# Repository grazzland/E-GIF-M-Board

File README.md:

# E-GIF-M-Board
Extendable Gateway and Industrial Firewall-ModBus

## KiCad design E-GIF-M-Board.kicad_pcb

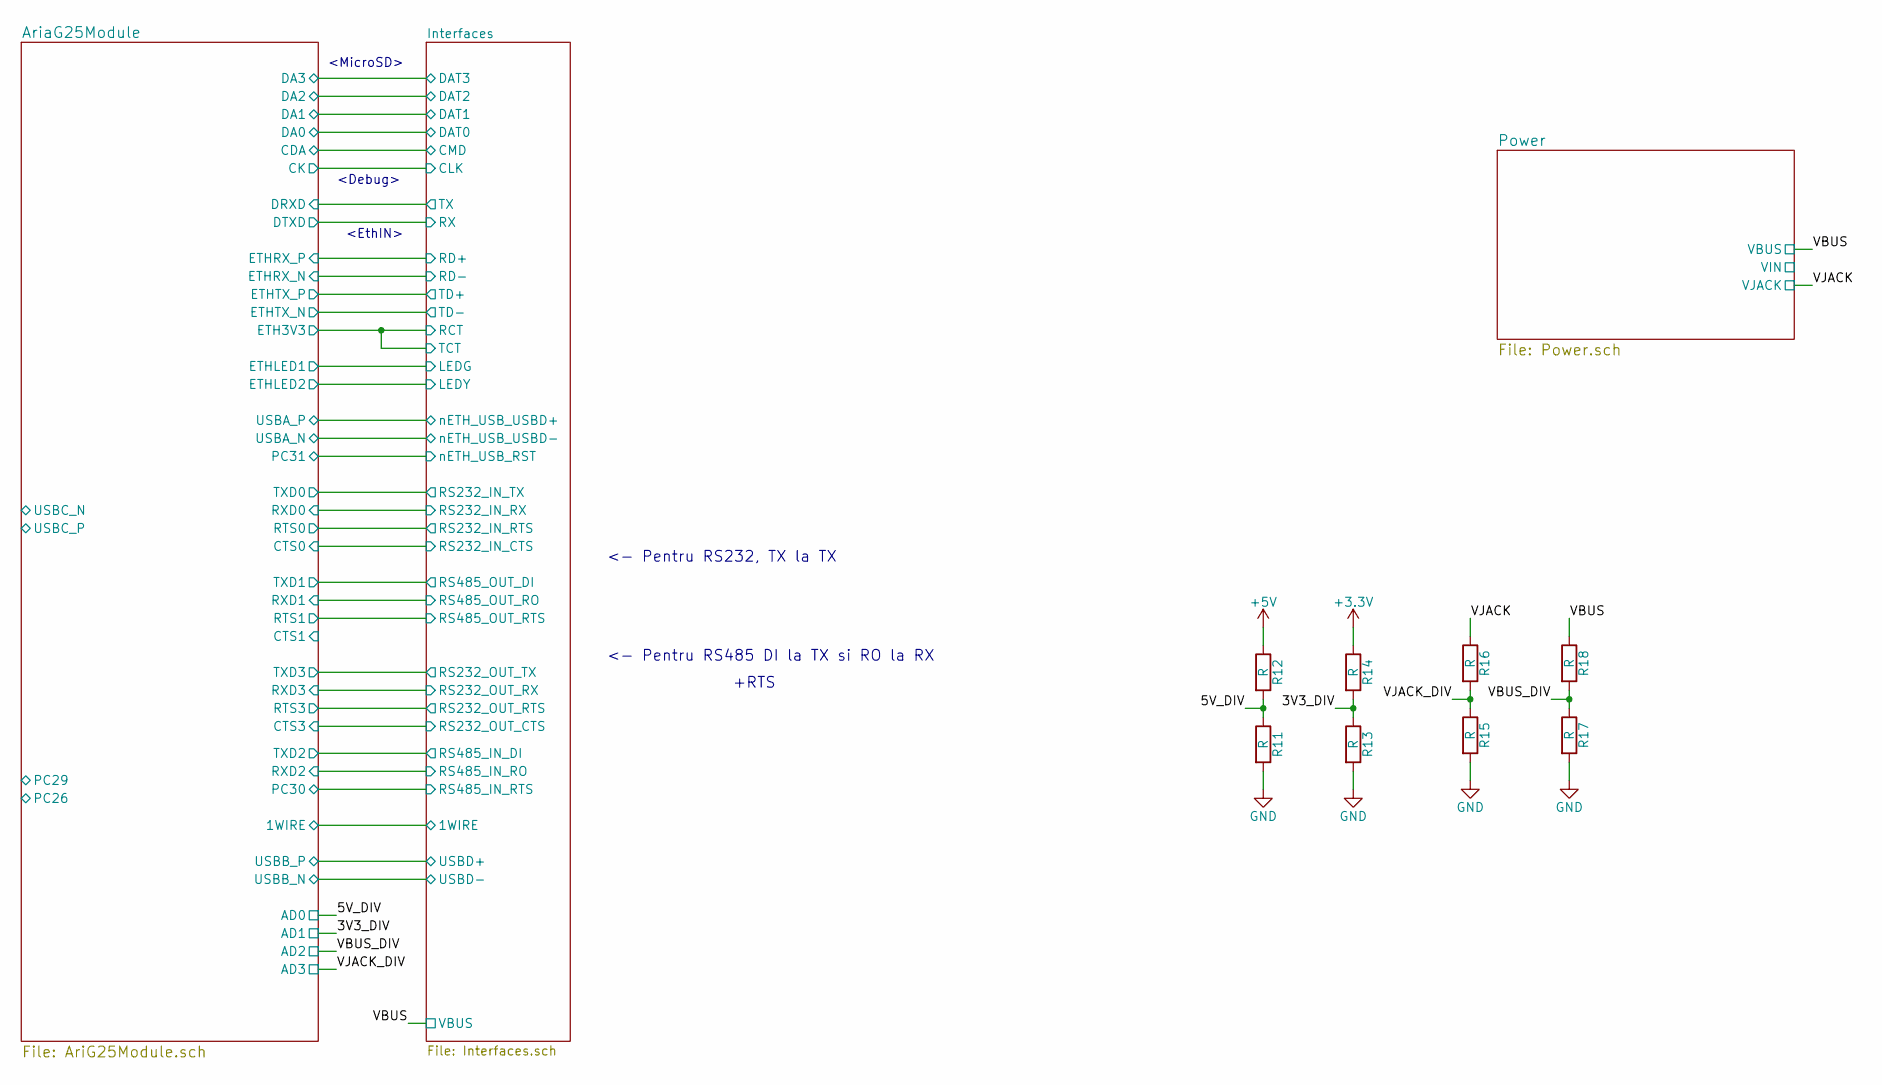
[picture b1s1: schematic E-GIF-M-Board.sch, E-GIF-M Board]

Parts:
R11, R12, R13, R14, R15, R16, R17, R18: R

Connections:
+3V3: R14.1; also elsewhere on the board
+5V: R12.1; also elsewhere on the board
/3V3_DIV: R13.1, R14.2; also elsewhere on the board
/5V_DIV: R11.1, R12.2; also elsewhere on the board
/VBUS: R18.1; also elsewhere on the board
/VBUS_DIV: R17.1, R18.2; also elsewhere on the board
/VJACK: R16.1; also elsewhere on the board
/VJACK_DIV: R15.1, R16.2; also elsewhere on the board
GND: R11.2, R13.2, R15.2, R17.2; also elsewhere on the board

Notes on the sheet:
<MicroSD>
<Debug>
<EthIN>
<- Pentru RS232, TX la TX
<- Pentru RS485 DI la TX si RO la RX
+RTS

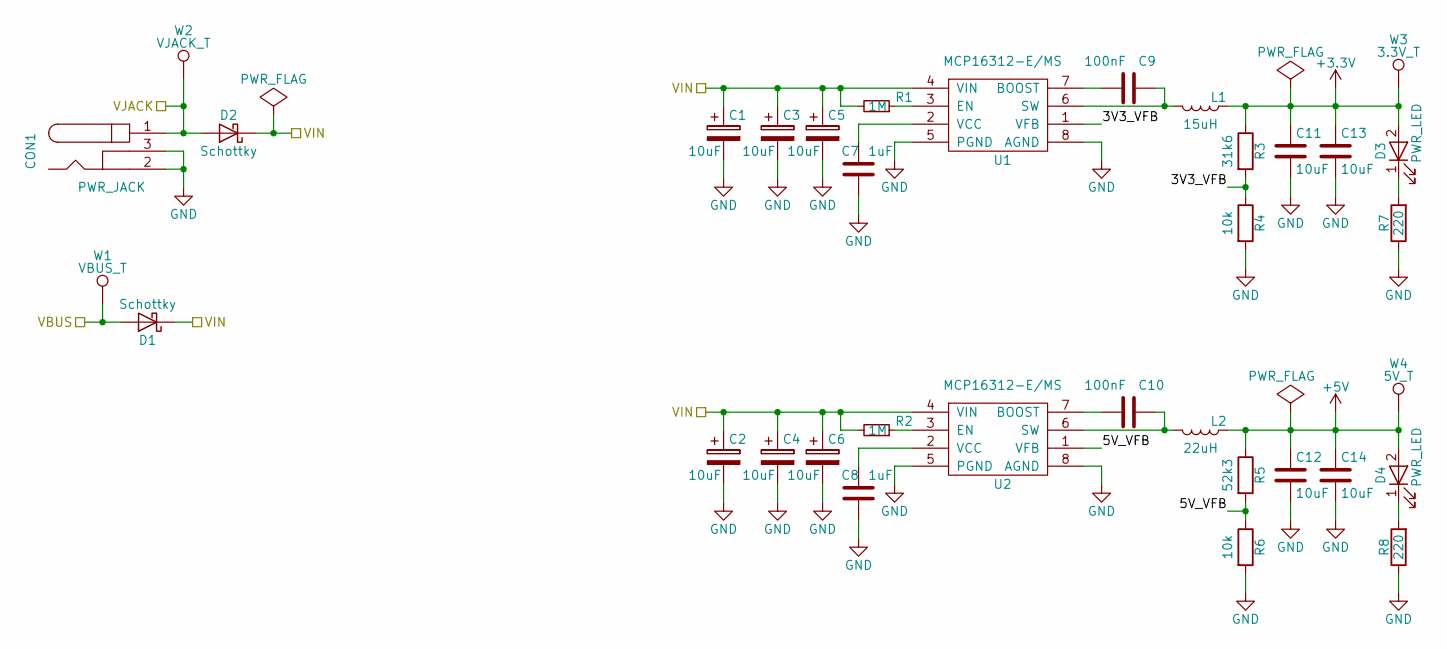
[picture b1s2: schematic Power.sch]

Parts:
C1, C2, C3, C4, C5, C6: 10uF; CP_Tantalum_Case-B_EIA-3528-21_Hand
C7, C8: 1uF; C_0603_HandSoldering
C9, C10: 100nF; C_0603_HandSoldering
C11, C12, C13, C14: 10uF; C_0603_HandSoldering
CON1: PWR_JACK; BARREL_JACK
D1, D2: Schottky; D_SMA-SMB_Universal_Handsoldering
D3, D4: PWR_LED; LED_0603
L1: 15uH; Inductor_Taiyo-Yuden_MD-5050
L2: 22uH; Inductor_Taiyo-Yuden_MD-5050
R1, R2: 1M; R_0603_HandSoldering
R3: 31k6; R_0603_HandSoldering
R4, R6: 10k; R_0603_HandSoldering
R5: 52k3; R_0603_HandSoldering
R7, R8: 220; R_0603_HandSoldering
U1, U2: MCP16312-E/MS; MSOP-8_3x3mm_Pitch0.65mm
W1: VBUS_T; Measurement_Point_Round-SMD-Pad_Small
W2: VJACK_T; Measurement_Point_Round-SMD-Pad_Small
W3: 3.3V_T; Measurement_Point_Round-SMD-Pad_Small
W4: 5V_T; Measurement_Point_Round-SMD-Pad_Small

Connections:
+3V3: C11.1, C13.1, D3.2 (A), L1.1, R3.1, W3.1; also elsewhere on the board
+5V: C12.1, C14.1, D4.2 (A), L2.1, R5.1, W4.1; also elsewhere on the board
/Power/3V3_VFB: R3.2, R4.1, U1.1 (VFB)
/Power/5V_VFB: R5.2, R6.1, U2.1 (VFB)
/Power/VIN: C1.1, C2.1, C3.1, C4.1, C5.1, C6.1, D1.1 (K), D2.1 (K), R1.2, R2.2, U1.4 (VIN), U2.4 (VIN)
/VBUS: D1.2 (A), W1.1; also elsewhere on the board
/VJACK: CON1.1, D2.2 (A), W2.1; also elsewhere on the board
GND: C1.2, C2.2, C3.2, C4.2, C5.2, C6.2, C7.2, C8.2, C11.2, C12.2, C13.2, C14.2, CON1.2, CON1.3, R4.2, R6.2, R7.1, R8.1, U1.5 (PGND), U1.8 (AGND), U2.5 (PGND), U2.8 (AGND); also elsewhere on the board
unnamed: C7.1, U1.2 (VCC)
unnamed: C8.1, U2.2 (VCC)
unnamed: C9.1, L1.2, U1.6 (SW)
unnamed: C9.2, U1.7 (BOOST)
unnamed: C10.1, L2.2, U2.6 (SW)
unnamed: C10.2, U2.7 (BOOST)
unnamed: D3.1 (K), R7.2
unnamed: D4.1 (K), R8.2
unnamed: R1.1, U1.3 (EN)
unnamed: R2.1, U2.3 (EN)

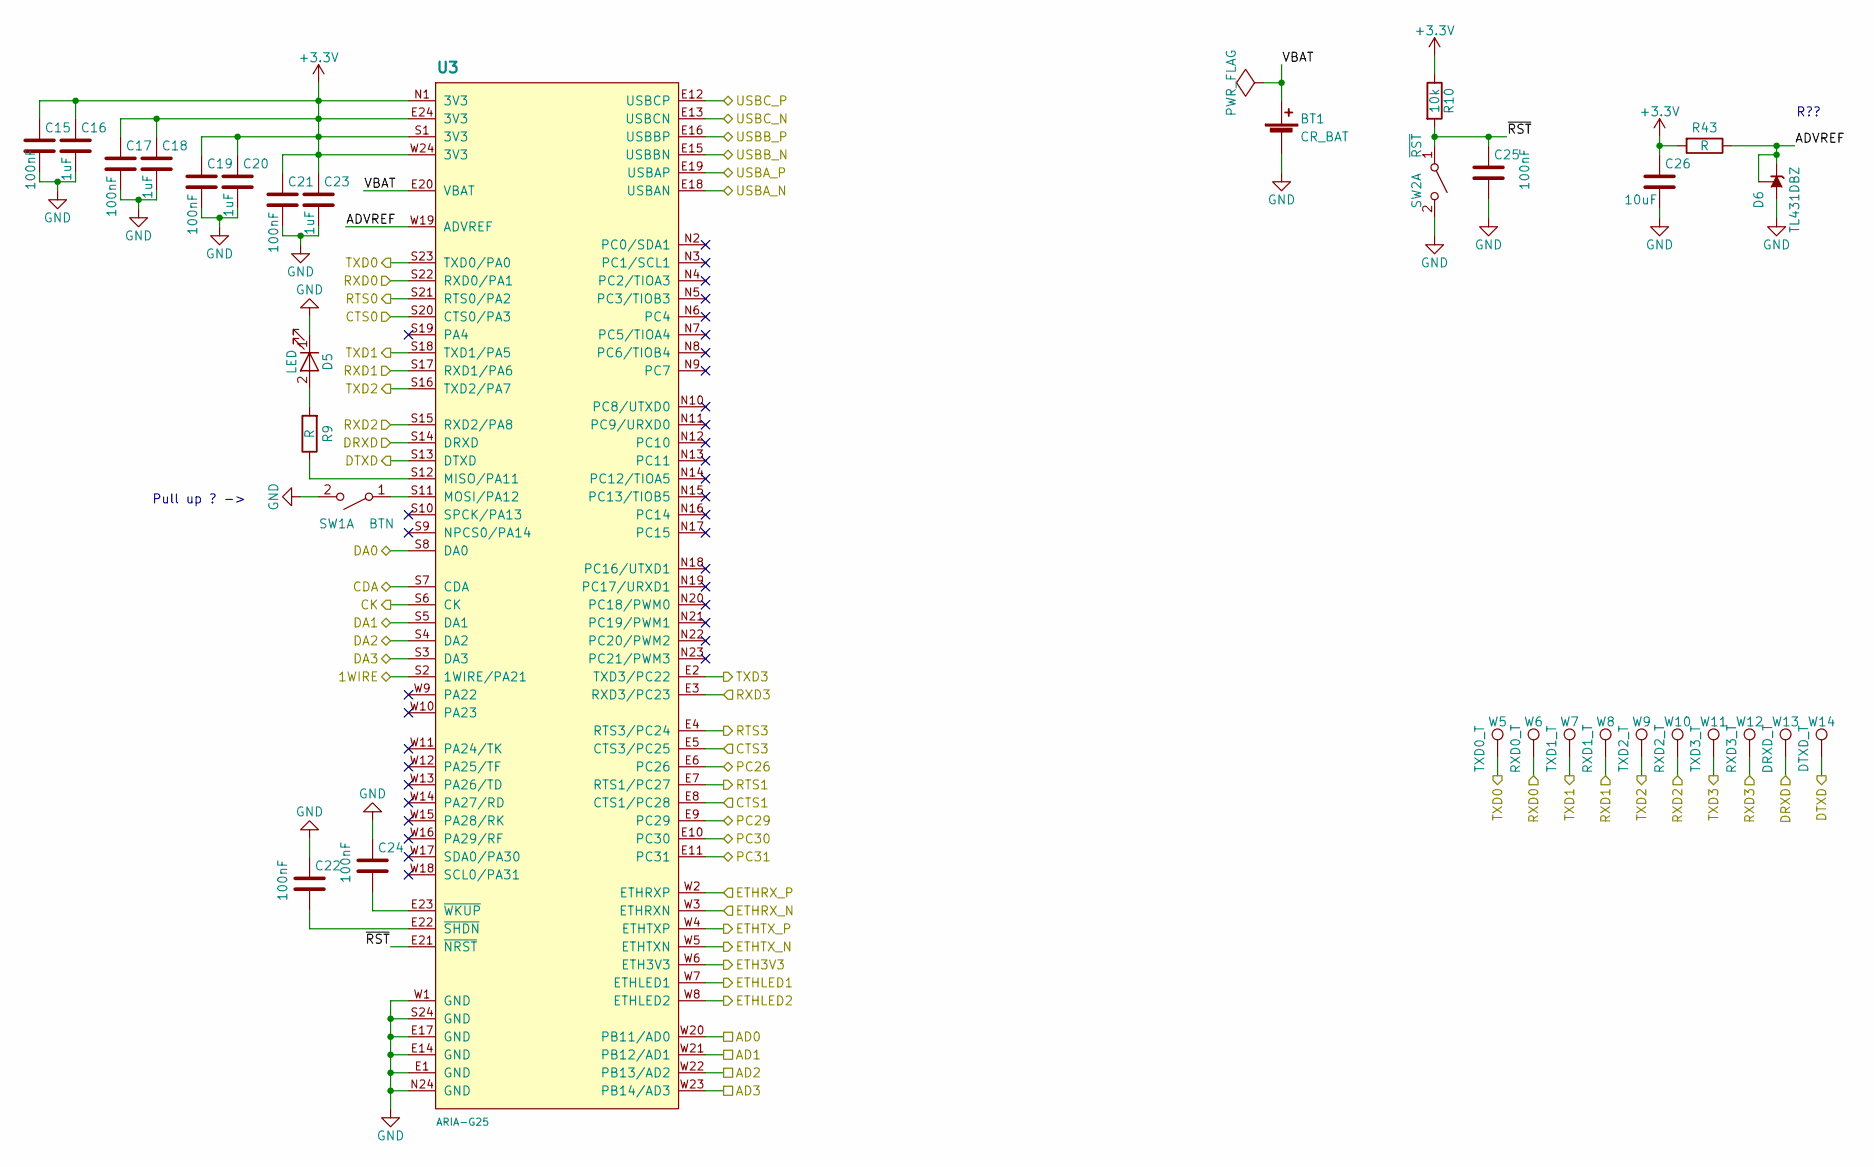
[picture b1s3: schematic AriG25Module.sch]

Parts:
BT1: CR_BAT; BatteryHolder_CoinCell_Keystone_3001
C15, C17, C19, C21, C22, C24, C25: 100nF; C_0603_HandSoldering
C16, C18, C20, C23: 1uF; C_0603_HandSoldering
C26: 10uF; C_0603_HandSoldering
D5: LED; LED_0603
D6: TL431DBZ; SOT-23
R9, R43: R; R_0603_HandSoldering
R10: 10k; R_0603_HandSoldering
SW1: BTN; SW_SPST_EVQPE1
SW2: ~RST; SW_SPST_EVQPE1
U3: ARIA-G25
W5: TXD0_T; Measurement_Point_Round-SMD-Pad_Small
W6: RXD0_T; Measurement_Point_Round-SMD-Pad_Small
W7: TXD1_T; Measurement_Point_Round-SMD-Pad_Small
W8: RXD1_T; Measurement_Point_Round-SMD-Pad_Small
W9: TXD2_T; Measurement_Point_Round-SMD-Pad_Small
W10: RXD2_T; Measurement_Point_Round-SMD-Pad_Small
W11: TXD3_T; Measurement_Point_Round-SMD-Pad_Small
W12: RXD3_T; Measurement_Point_Round-SMD-Pad_Small
W13: DRXD_T; Measurement_Point_Round-SMD-Pad_Small
W14: DTXD_T; Measurement_Point_Round-SMD-Pad_Small

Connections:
+3V3: C15.1, C16.1, C17.1, C18.1, C19.1, C20.1, C21.1, C23.1, C26.1, R10.1, R43.2, U3.E24 (3V3), U3.N1 (3V3), U3.S1 (3V3), U3.W24 (3V3); also elsewhere on the board
/3V3_DIV: U3.W21 (PB12/AD1); also elsewhere on the board
/5V_DIV: U3.W20 (PB11/AD0); also elsewhere on the board
/AriaG25Module/1WIRE: U3.S2 (1WIRE/PA21); also elsewhere on the board
/AriaG25Module/ADVREF: D6.1 (K), D6.2 (REF), R43.1, U3.W19 (ADVREF)
/AriaG25Module/CDA: U3.S7 (CDA); also elsewhere on the board
/AriaG25Module/CK: U3.S6 (CK); also elsewhere on the board
/AriaG25Module/CTS0: U3.S20 (CTS0/PA3); also elsewhere on the board
/AriaG25Module/CTS1: U3.E8 (CTS1/PC28)
/AriaG25Module/CTS3: U3.E5 (CTS3/PC25); also elsewhere on the board
/AriaG25Module/DA0: U3.S8 (DA0); also elsewhere on the board
/AriaG25Module/DA1: U3.S5 (DA1); also elsewhere on the board
/AriaG25Module/DA2: U3.S4 (DA2); also elsewhere on the board
/AriaG25Module/DA3: U3.S3 (DA3); also elsewhere on the board
/AriaG25Module/DRXD: U3.S14 (DRXD), W13.1; also elsewhere on the board
/AriaG25Module/DTXD: U3.S13 (DTXD), W14.1; also elsewhere on the board
/AriaG25Module/ETH3V3: U3.W6 (ETH3V3); also elsewhere on the board
/AriaG25Module/ETHLED1: U3.W7 (ETHLED1); also elsewhere on the board
/AriaG25Module/ETHLED2: U3.W8 (ETHLED2); also elsewhere on the board
/AriaG25Module/ETHRX_N: U3.W3 (ETHRXN); also elsewhere on the board
/AriaG25Module/ETHRX_P: U3.W2 (ETHRXP); also elsewhere on the board
/AriaG25Module/ETHTX_N: U3.W5 (ETHTXN); also elsewhere on the board
/AriaG25Module/ETHTX_P: U3.W4 (ETHTXP); also elsewhere on the board
/AriaG25Module/PC26: U3.E6 (PC26)
/AriaG25Module/PC29: U3.E9 (PC29)
/AriaG25Module/PC30: U3.E10 (PC30); also elsewhere on the board
/AriaG25Module/PC31: U3.E11 (PC31); also elsewhere on the board
/AriaG25Module/USBA_N: U3.E18 (USBAN); also elsewhere on the board
/AriaG25Module/USBA_P: U3.E19 (USBAP); also elsewhere on the board
/AriaG25Module/USBB_N: U3.E15 (USBBN); also elsewhere on the board
/AriaG25Module/USBB_P: U3.E16 (USBBP); also elsewhere on the board
/AriaG25Module/USBC_N: U3.E13 (USBCN)
/AriaG25Module/USBC_P: U3.E12 (USBCP)
/AriaG25Module/VBAT: BT1.1 (+), U3.E20 (VBAT)
/AriaG25Module/~RST: C25.1, R10.2, SW2.1 (A), U3.E21 (~NRST)
/Interfaces/RS232_IN_RTS: U3.S21 (RTS0/PA2); also elsewhere on the board
/Interfaces/RS232_IN_RX: U3.S22 (RXD0/PA1), W6.1; also elsewhere on the board
/Interfaces/RS232_IN_TX: U3.S23 (TXD0/PA0), W5.1; also elsewhere on the board
/Interfaces/RS232_OUT_RTS: U3.E4 (RTS3/PC24); also elsewhere on the board
/Interfaces/RS232_OUT_RX: U3.E3 (RXD3/PC23), W12.1; also elsewhere on the board
/Interfaces/RS232_OUT_TX: U3.E2 (TXD3/PC22), W11.1; also elsewhere on the board
/Interfaces/RS485_IN_DI: U3.S16 (TXD2/PA7), W9.1; also elsewhere on the board
/Interfaces/RS485_IN_RO: U3.S15 (RXD2/PA8), W10.1; also elsewhere on the board
/Interfaces/RS485_OUT_DI: U3.S18 (TXD1/PA5), W7.1; also elsewhere on the board
/Interfaces/RS485_OUT_RO: U3.S17 (RXD1/PA6), W8.1; also elsewhere on the board
/Interfaces/RS485_OUT_RTS: U3.E7 (RTS1/PC27); also elsewhere on the board
/VBUS_DIV: U3.W22 (PB13/AD2); also elsewhere on the board
/VJACK_DIV: U3.W23 (PB14/AD3); also elsewhere on the board
GND: BT1.2 (-), C15.2, C16.2, C17.2, C18.2, C19.2, C20.2, C21.2, C22.1, C23.2, C24.1, C25.2, C26.2, D5.1 (K), D6.3 (A), SW1.2 (B), SW2.2 (B), U3.E1 (GND), U3.E14 (GND), U3.E17 (GND), U3.GND, U3.N24 (GND), U3.S24 (GND), U3.W1 (GND); also elsewhere on the board
unnamed: C22.2, U3.E22 (~SHDN)
unnamed: C24.2, U3.E23 (~WKUP)
unnamed: D5.2 (A), R9.2
unnamed: R9.1, U3.S12 (MISO/PA11)
unnamed: SW1.1 (A), U3.S11 (MOSI/PA12)

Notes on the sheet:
R??
Pull up ? ->

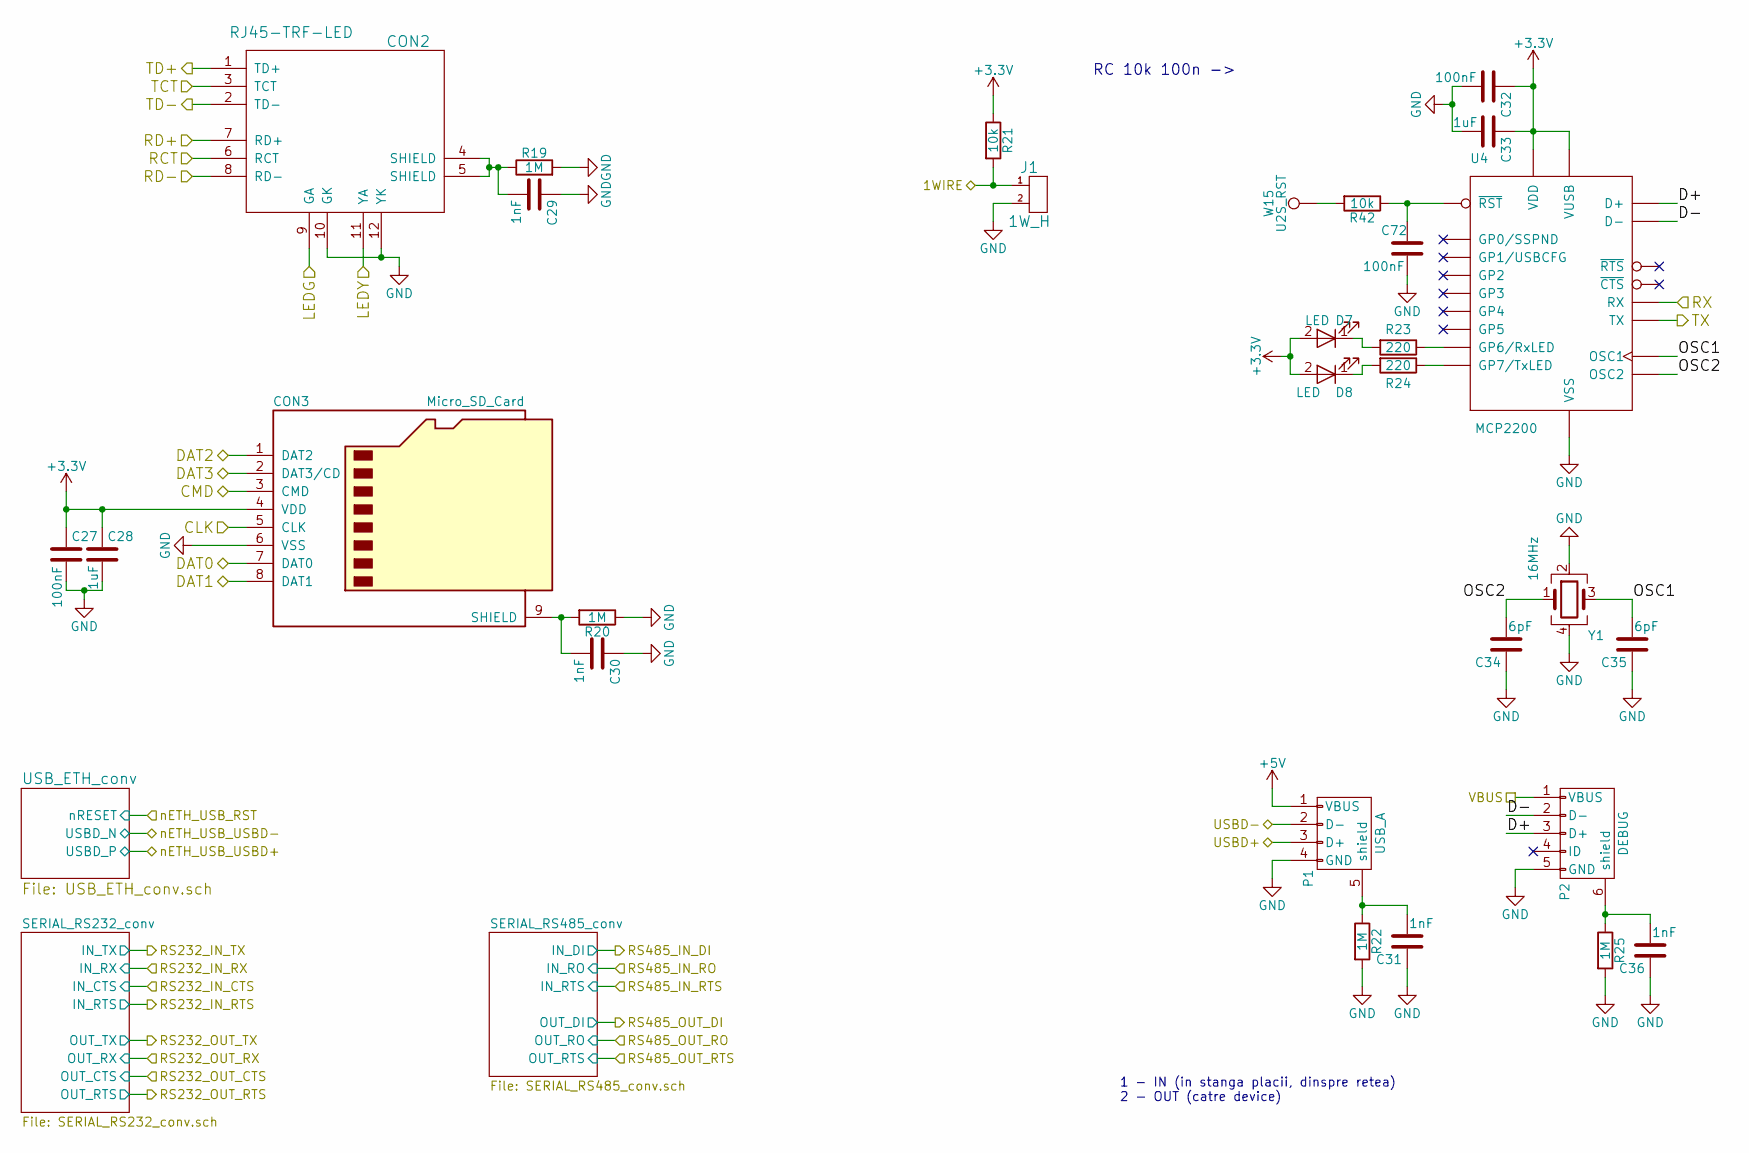
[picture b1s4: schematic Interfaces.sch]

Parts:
C27, C32, C72: 100nF; C_0603_HandSoldering
C28, C33: 1uF; C_0603_HandSoldering
C29, C30, C31, C36: 1nF; C_0603_HandSoldering
C34, C35: 6pF; C_0603_HandSoldering
CON2: RJ45-TRF-LED; RJ45_TRANSFO
CON3: Micro_SD_Card; MicroSDSocket
D7, D8: LED; LED_0603
J1: 1W_H; Pin_Header_Straight_1x02_Pitch1.27mm
P1: USB_A
P2: DEBUG; MicroUSB-B
R19, R20, R22, R25: 1M; R_0603_HandSoldering
R21, R42: 10k; R_0603_HandSoldering
R23, R24: 220; R_0603_HandSoldering
U4: MCP2200; SSOP-20_4.4x6.5mm_Pitch0.65mm
W15: U2S_RST; Measurement_Point_Round-SMD-Pad_Small
Y1: 16MHz; Crystal_SMD_3225-4pin_3.2x2.5mm_HandSoldering

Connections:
+3V3: C27.1, C28.1, C32.1, C33.1, CON3.4 (VDD), D7.2 (A), D8.2 (A), R21.1, U4.1 (VDD), U4.17 (VUSB); also elsewhere on the board
+5V: P1.1 (VBUS); also elsewhere on the board
/AriaG25Module/1WIRE: J1.1, R21.2; also elsewhere on the board
/AriaG25Module/CDA: CON3.3 (CMD); also elsewhere on the board
/AriaG25Module/CK: CON3.5 (CLK); also elsewhere on the board
/AriaG25Module/DA0: CON3.7 (DAT0); also elsewhere on the board
/AriaG25Module/DA1: CON3.8 (DAT1); also elsewhere on the board
/AriaG25Module/DA2: CON3.1 (DAT2); also elsewhere on the board
/AriaG25Module/DA3: CON3.2 (DAT3/CD); also elsewhere on the board
/AriaG25Module/DRXD: U4.10 (TX); also elsewhere on the board
/AriaG25Module/DTXD: U4.12 (RX); also elsewhere on the board
/AriaG25Module/ETH3V3: CON2.3 (TCT), CON2.6 (RCT); also elsewhere on the board
/AriaG25Module/ETHLED1: CON2.9 (GA); also elsewhere on the board
/AriaG25Module/ETHLED2: CON2.11 (YA); also elsewhere on the board
/AriaG25Module/ETHRX_N: CON2.8 (RD-); also elsewhere on the board
/AriaG25Module/ETHRX_P: CON2.7 (RD+); also elsewhere on the board
/AriaG25Module/ETHTX_N: CON2.2 (TD-); also elsewhere on the board
/AriaG25Module/ETHTX_P: CON2.1 (TD+); also elsewhere on the board
/AriaG25Module/USBB_N: P1.2 (D-); also elsewhere on the board
/AriaG25Module/USBB_P: P1.3 (D+); also elsewhere on the board
/Interfaces/D+: P2.3 (D+), U4.19 (D+)
/Interfaces/D-: P2.2 (D-), U4.18 (D-)
/Interfaces/OSC1: C35.2, U4.2 (OSC1), Y1.3
/Interfaces/OSC2: C34.2, U4.3 (OSC2), Y1.1
/VBUS: P2.1 (VBUS); also elsewhere on the board
GND: C27.2, C28.2, C29.1, C30.1, C31.1, C32.2, C33.2, C34.1, C35.1, C36.1, C72.2, CON2.10 (GK), CON2.12 (YK), CON3.6 (VSS), J1.2, P1.4 (GND), P2.5 (GND), R19.2, R20.1, R22.2, R25.2, U4.20 (VSS), Y1.2, Y1.4; also elsewhere on the board
unnamed: C29.2, CON2.4 (SHIELD), CON2.5 (SHIELD), R19.1
unnamed: C30.2, CON3.9 (SHIELD), R20.2
unnamed: C31.2, P1.5 (shield), R22.1
unnamed: C36.2, P2.6 (shield), R25.1
unnamed: C72.1, R42.1, U4.4 (~RST)
unnamed: D7.1 (K), R23.2
unnamed: D8.1 (K), R24.2
unnamed: R23.1, U4.6 (GP6/RxLED)
unnamed: R24.1, U4.5 (GP7/TxLED)
unnamed: R42.2, W15.1

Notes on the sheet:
1 - IN (in stanga placii, dinspre retea) 2 - OUT (catre device)
RC 10k 100n ->

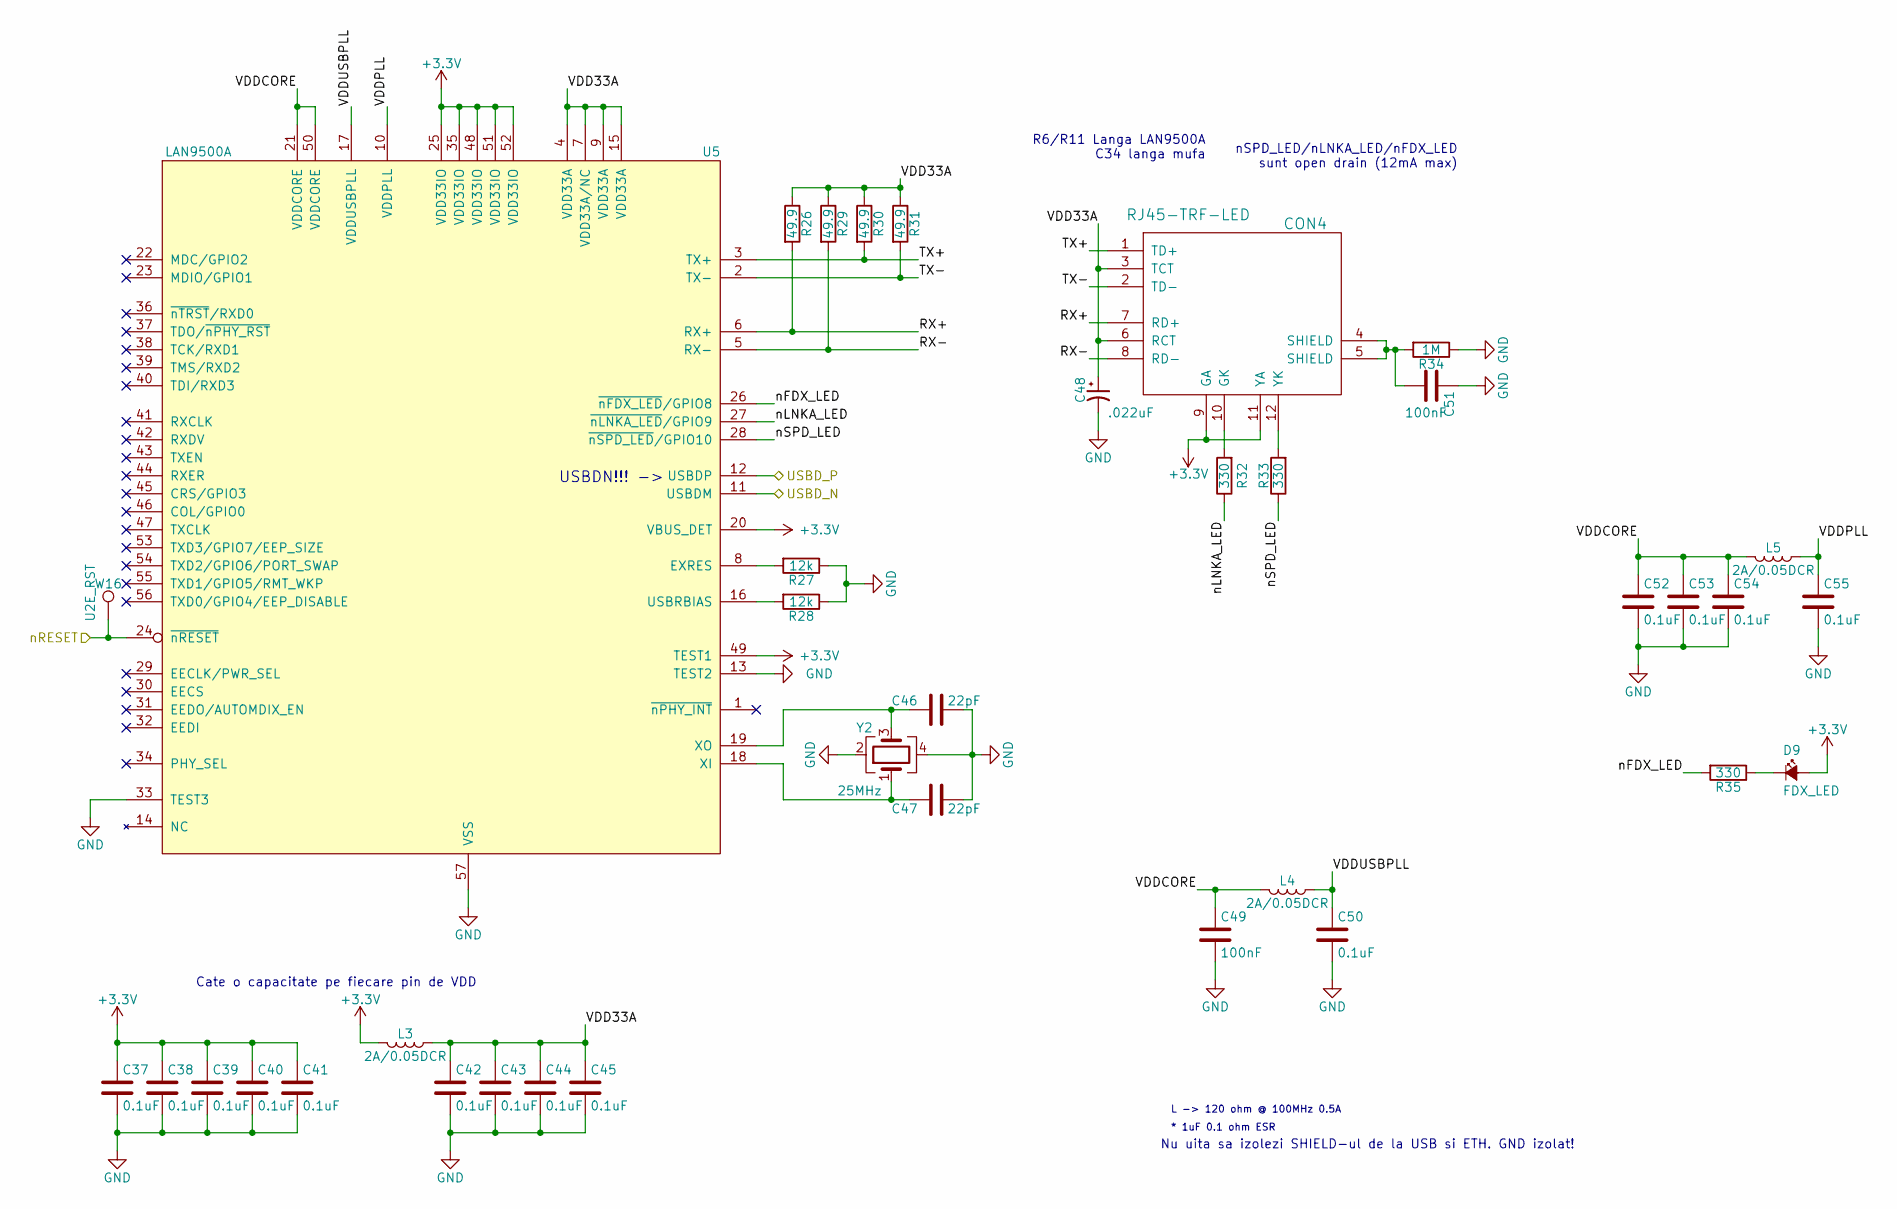
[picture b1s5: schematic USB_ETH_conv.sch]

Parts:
C37, C38, C39, C40, C41, C42, C43, C44, C45, C50, C52, C53, C54, C55: 0.1uF; C_0603_HandSoldering
C46, C47: 22pF; C_0603_HandSoldering
C48: .022uF; CP_Tantalum_Case-C_EIA-6032-28_Hand
C49, C51: 100nF; C_0603_HandSoldering
CON4: RJ45-TRF-LED; RJ45_TRANSFO
D9: FDX_LED; LED_0603
L3, L4, L5: 2A/0.05DCR; R_0603_HandSoldering
R26, R29, R30, R31: 49.9; R_0603_HandSoldering
R27, R28: 12k; R_0603_HandSoldering
R32, R33, R35: 330; R_0603_HandSoldering
R34: 1M; R_0603_HandSoldering
U5: LAN9500A; QFN-56-1EP_7x7mm_Pitch0.4mm
W16: U2E_RST; Measurement_Point_Round-SMD-Pad_Small
Y2: 25MHz; Crystal_SMD_3225-4pin_3.2x2.5mm_HandSoldering

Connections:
+3V3: C37.1, C38.1, C39.1, C40.1, C41.1, CON4.9 (GA), CON4.11 (YA), D9.2 (A), L3.2, U5.20 (VBUS_DET), U5.25 (VDD33IO), U5.35 (VDD33IO), U5.48 (VDD33IO), U5.49 (TEST1), U5.51 (VDD33IO), U5.52 (VDD33IO); also elsewhere on the board
/AriaG25Module/PC31: U5.24 (~nRESET), W16.1; also elsewhere on the board
/AriaG25Module/USBA_N: U5.11 (USBDM); also elsewhere on the board
/AriaG25Module/USBA_P: U5.12 (USBDP); also elsewhere on the board
/Interfaces/USB_ETH_conv/RX+: CON4.7 (RD+), R26.2, U5.6 (RX+)
/Interfaces/USB_ETH_conv/RX-: CON4.8 (RD-), R29.2, U5.5 (RX-)
/Interfaces/USB_ETH_conv/TX+: CON4.1 (TD+), R30.2, U5.3 (TX+)
/Interfaces/USB_ETH_conv/TX-: CON4.2 (TD-), R31.2, U5.2 (TX-)
/Interfaces/USB_ETH_conv/VDD33A: C42.1, C43.1, C44.1, C45.1, C48.1, CON4.3 (TCT), CON4.6 (RCT), L3.1, R26.1, R29.1, R30.1, R31.1, U5.4 (VDD33A), U5.7 (VDD33A/NC), U5.9 (VDD33A), U5.15 (VDD33A)
/Interfaces/USB_ETH_conv/VDDCORE: C49.1, C52.1, C53.1, C54.1, L4.2, L5.2, U5.21 (VDDCORE), U5.50 (VDDCORE)
/Interfaces/USB_ETH_conv/VDDPLL: C55.1, L5.1, U5.10 (VDDPLL)
/Interfaces/USB_ETH_conv/VDDUSBPLL: C50.1, L4.1, U5.17 (VDDUSBPLL)
/Interfaces/USB_ETH_conv/nFDX_LED: R35.2, U5.26 (~nFDX_LED~/GPIO8)
/Interfaces/USB_ETH_conv/nLNKA_LED: R32.1, U5.27 (~nLNKA_LED~/GPIO9)
/Interfaces/USB_ETH_conv/nSPD_LED: R33.1, U5.28 (~nSPD_LED~/GPIO10)
GND: C37.2, C38.2, C39.2, C40.2, C41.2, C42.2, C43.2, C44.2, C45.2, C46.2, C47.2, C48.2, C49.2, C50.2, C51.1, C52.2, C53.2, C54.2, C55.2, R27.1, R28.1, R34.1, U5.13 (TEST2), U5.33 (TEST3), U5.57 (VSS), Y2.2, Y2.4; also elsewhere on the board
unnamed: C46.1, U5.19 (XO), Y2.3
unnamed: C47.1, U5.18 (XI), Y2.1
unnamed: C51.2, CON4.4 (SHIELD), CON4.5 (SHIELD), R34.2
unnamed: CON4.10 (GK), R32.2
unnamed: CON4.12 (YK), R33.2
unnamed: D9.1 (K), R35.1
unnamed: R27.2, U5.8 (EXRES)
unnamed: R28.2, U5.16 (USBRBIAS)

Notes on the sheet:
L -> 120 ohm @ 100MHz 0.5A
* 1uF 0.1 ohm ESR
Nu uita sa izolezi SHIELD-ul de la USB si ETH. GND izolat!
nSPD_LED/nLNKA_LED/nFDX_LED sunt open drain (12mA max)
R6/R11 Langa LAN9500A C34 langa mufa
Cate o capacitate pe fiecare pin de VDD
USBDN!!! ->

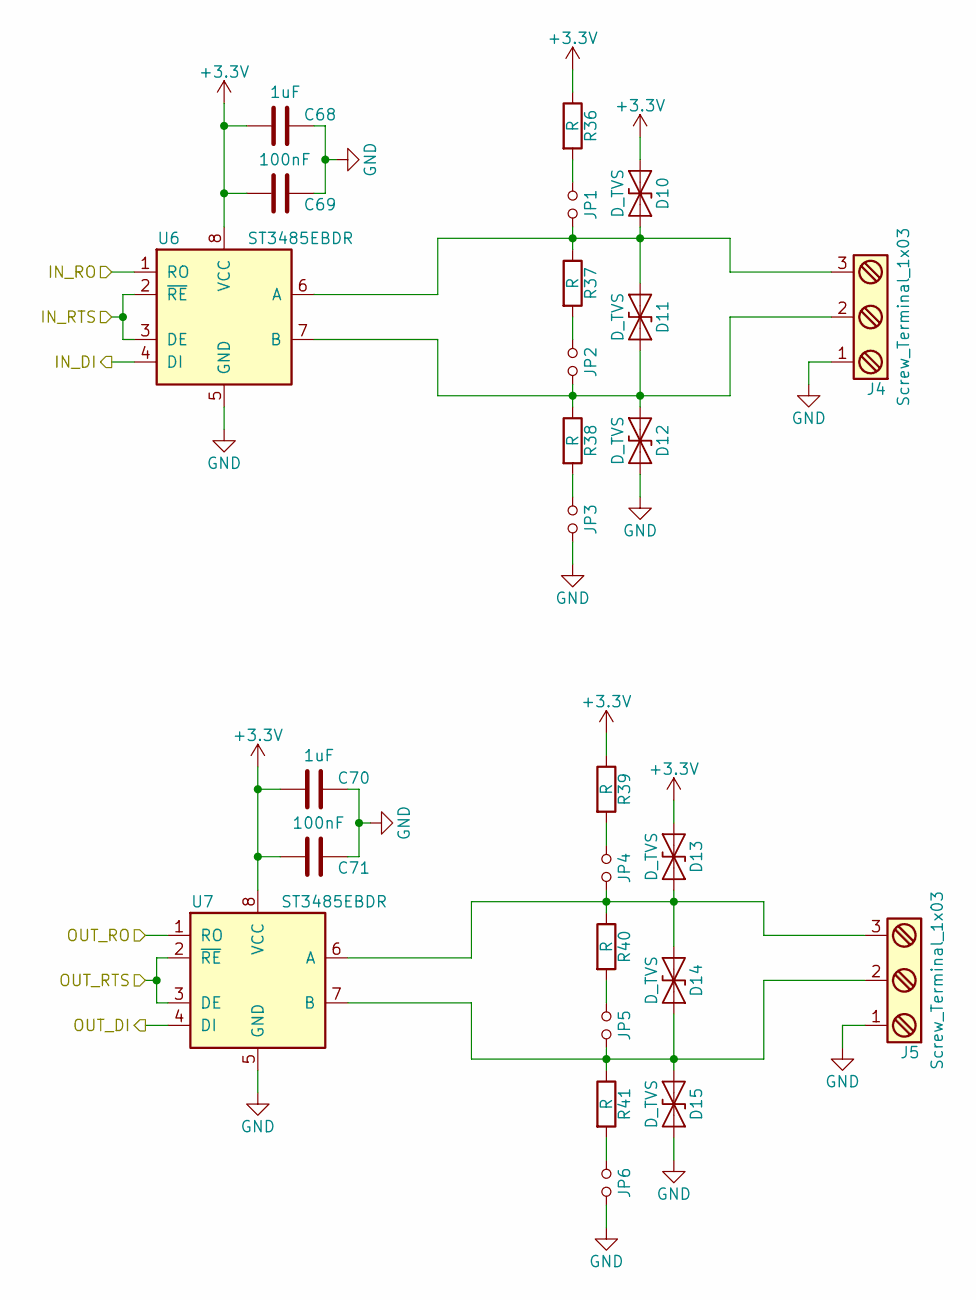
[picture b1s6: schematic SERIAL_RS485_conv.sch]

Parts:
C68, C70: 1uF; C_0603_HandSoldering
C69, C71: 100nF; C_0603_HandSoldering
D10, D11, D12, D13, D14, D15: D_TVS; D_SMA-SMB_Universal_Handsoldering
J4, J5: Screw_Terminal_1x03; TerminalBlock_Pheonix_PT-3.5mm_3pol
JP1, JP2, JP3, JP4, JP5, JP6: Jumper_NO_Small; Pin_Header_Straight_1x02_Pitch2.54mm
R36, R37, R38, R39, R40, R41: R; R_0603_HandSoldering
U6, U7: ST3485EBDR; SO-8

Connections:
+3V3: C68.2, C69.2, C70.2, C71.2, D10.1 (A1), D13.1 (A1), R36.1, R39.1, U6.8 (VCC), U7.8 (VCC); also elsewhere on the board
/AriaG25Module/PC30: U6.2 (~RE~), U6.3 (DE); also elsewhere on the board
/Interfaces/RS485_IN_DI: U6.4 (DI); also elsewhere on the board
/Interfaces/RS485_IN_RO: U6.1 (RO); also elsewhere on the board
/Interfaces/RS485_OUT_DI: U7.4 (DI); also elsewhere on the board
/Interfaces/RS485_OUT_RO: U7.1 (RO); also elsewhere on the board
/Interfaces/RS485_OUT_RTS: U7.2 (~RE~), U7.3 (DE); also elsewhere on the board
GND: C68.1, C69.1, C70.1, C71.1, D12.2 (A2), D15.2 (A2), J4.1, J5.1, JP3.2, JP6.2, U6.5 (GND), U7.5 (GND); also elsewhere on the board
unnamed: D10.2 (A2), D11.1 (A1), J4.3, JP1.2, R37.1, U6.6 (A)
unnamed: D11.2 (A2), D12.1 (A1), J4.2, JP2.2, R38.1, U6.7 (B)
unnamed: D13.2 (A2), D14.1 (A1), J5.3, JP4.2, R40.1, U7.6 (A)
unnamed: D14.2 (A2), D15.1 (A1), J5.2, JP5.2, R41.1, U7.7 (B)
unnamed: JP1.1, R36.2
unnamed: JP2.1, R37.2
unnamed: JP3.1, R38.2
unnamed: JP4.1, R39.2
unnamed: JP5.1, R40.2
unnamed: JP6.1, R41.2

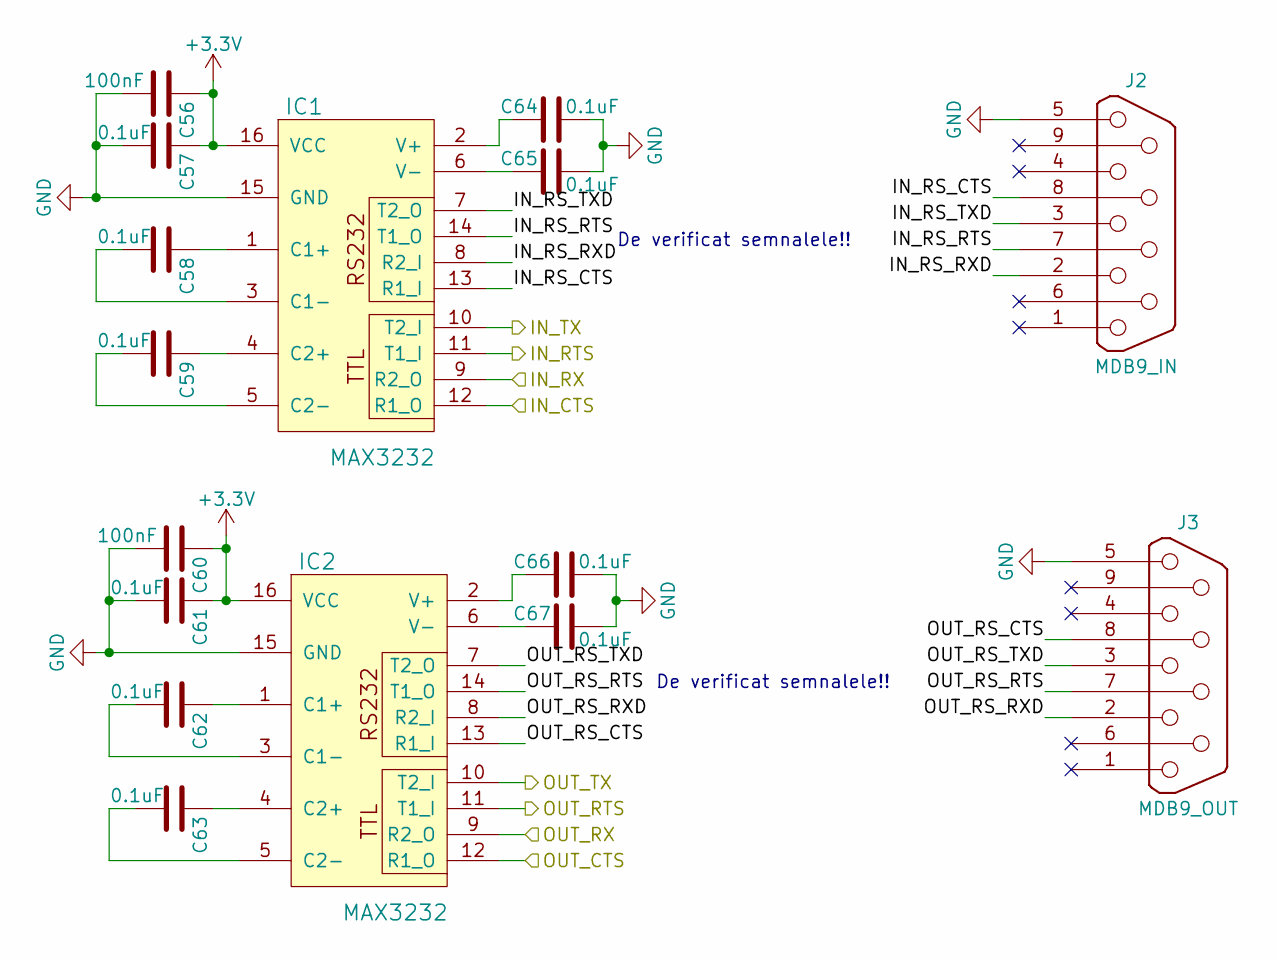
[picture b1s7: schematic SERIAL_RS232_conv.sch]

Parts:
C56, C60: 100nF; C_0603_HandSoldering
C57, C58, C59, C61, C62, C63, C64, C65, C66, C67: 0.1uF; C_0603_HandSoldering
IC1, IC2: MAX3232; SSOP-16_3.9x4.9mm_Pitch0.635mm
J2: MDB9_IN; DB9FC
J3: MDB9_OUT; DB9FC

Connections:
+3V3: C56.1, C57.1, C60.1, C61.1, IC1.16 (VCC), IC2.16 (VCC); also elsewhere on the board
/AriaG25Module/CTS0: IC1.12 (R1_O); also elsewhere on the board
/AriaG25Module/CTS3: IC2.12 (R1_O); also elsewhere on the board
/Interfaces/RS232_IN_RTS: IC1.11 (T1_I); also elsewhere on the board
/Interfaces/RS232_IN_RX: IC1.9 (R2_O); also elsewhere on the board
/Interfaces/RS232_IN_TX: IC1.10 (T2_I); also elsewhere on the board
/Interfaces/RS232_OUT_RTS: IC2.11 (T1_I); also elsewhere on the board
/Interfaces/RS232_OUT_RX: IC2.9 (R2_O); also elsewhere on the board
/Interfaces/RS232_OUT_TX: IC2.10 (T2_I); also elsewhere on the board
/Interfaces/SERIAL_RS232_conv/IN_RS_CTS: IC1.13 (R1_I), J2.8
/Interfaces/SERIAL_RS232_conv/IN_RS_RTS: IC1.14 (T1_O), J2.7
/Interfaces/SERIAL_RS232_conv/IN_RS_RXD: IC1.8 (R2_I), J2.2
/Interfaces/SERIAL_RS232_conv/IN_RS_TXD: IC1.7 (T2_O), J2.3
/Interfaces/SERIAL_RS232_conv/OUT_RS_CTS: IC2.13 (R1_I), J3.8
/Interfaces/SERIAL_RS232_conv/OUT_RS_RTS: IC2.14 (T1_O), J3.7
/Interfaces/SERIAL_RS232_conv/OUT_RS_RXD: IC2.8 (R2_I), J3.2
/Interfaces/SERIAL_RS232_conv/OUT_RS_TXD: IC2.7 (T2_O), J3.3
GND: C56.2, C57.2, C60.2, C61.2, C64.1, C65.1, C66.1, C67.1, IC1.15 (GND), IC2.15 (GND), J2.5, J3.5; also elsewhere on the board
unnamed: C58.1, IC1.1 (C1+)
unnamed: C58.2, IC1.3 (C1-)
unnamed: C59.1, IC1.4 (C2+)
unnamed: C59.2, IC1.5 (C2-)
unnamed: C62.1, IC2.1 (C1+)
unnamed: C62.2, IC2.3 (C1-)
unnamed: C63.1, IC2.4 (C2+)
unnamed: C63.2, IC2.5 (C2-)
unnamed: C64.2, IC1.2 (V+)
unnamed: C65.2, IC1.6 (V-)
unnamed: C66.2, IC2.2 (V+)
unnamed: C67.2, IC2.6 (V-)

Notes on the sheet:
De verificat semnalele!!
